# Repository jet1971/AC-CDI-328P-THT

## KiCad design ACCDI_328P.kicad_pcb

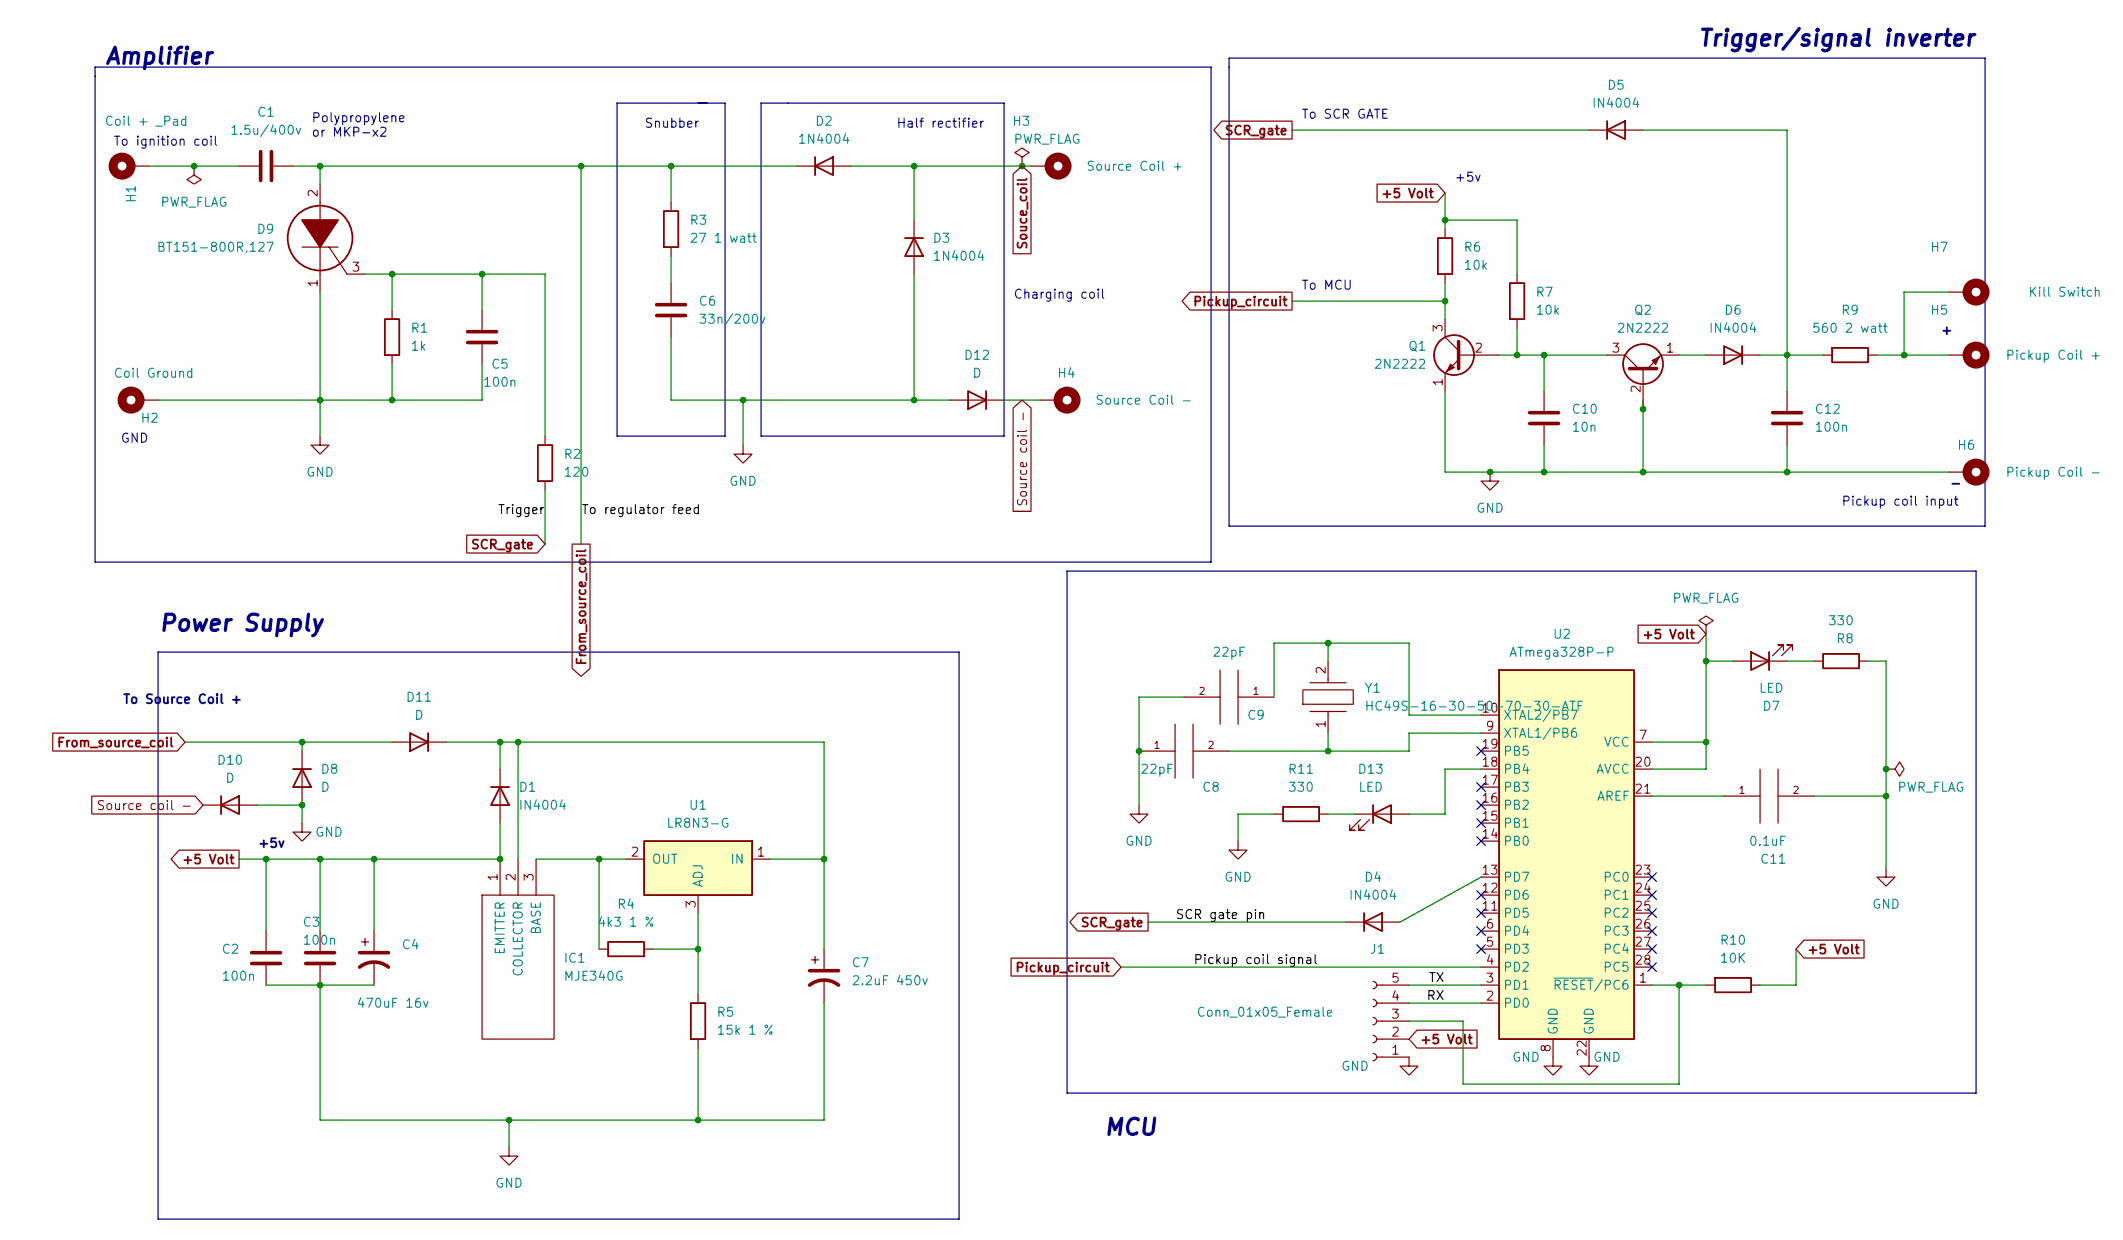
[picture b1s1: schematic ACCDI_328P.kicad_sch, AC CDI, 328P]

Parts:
C1: 1.5u/400v; C_Rect_L26.5mm_W5.0mm_P22.50mm_MKS4
C2, C3, C5, C12: 100n; C_Disc_D6.0mm_W2.5mm_P5.00mm
C4: 470uF 16v; C_Radial_D10.0mm_H16.0mm_P5.00mm
C6: 33n/200v; C_Rect_L9.0mm_W3.2mm_P7.50mm_MKT
C7: 2.2uF 450v; C_Radial_D10.0mm_H12.5mm_P5.00mm
C8, C9: 22pF; C_Disc_D5.0mm_W2.5mm_P5.00mm
C10: 10n; C_Disc_D6.0mm_W2.5mm_P5.00mm
C11: 0.1uF; C_Disc_D6.0mm_W2.5mm_P5.00mm
D1, D4, D5, D6: IN4004; D_DO-41_SOD81_P10.16mm_Horizontal
D2, D3: 1N4004; D_DO-41_SOD81_P10.16mm_Horizontal
D7, D13: LED; LED_D3.0mm
D8, D10, D11, D12: D; D_DO-41_SOD81_P10.16mm_Horizontal
D9: BT151-800R,127; TO254P470X1000X2000-3P; Manufacturer_Part_Number BT151-800R,127; Mouser Part Number 771-BT151-800R127
H1: Coil + _Pad; MountingHole_2.2mm_M2_ISO14580_Pad_TopBottom
H2: Coil Ground; MountingHole_2.2mm_M2_Pad_TopBottom
H3: Source Coil +; MountingHole_2.2mm_M2_Pad_TopBottom
H4: Source Coil -; MountingHole_2.2mm_M2_Pad_TopBottom
H5: Pickup Coil +; MountingHole_2.2mm_M2_Pad_TopBottom
H6: Pickup Coil -; MountingHole_2.2mm_M2_Pad_TopBottom
H7: Kill Switch; MountingHole_2.2mm_M2_Pad_TopBottom
IC1: MJE340G; TO229P300X760X1364-3P; Manufacturer_Part_Number MJE340G; Mouser Part Number 863-MJE340G
J1: Conn_01x05_Female; PinSocket_1x05_P2.54mm_Vertical
Q1, Q2: 2N2222; TO-92_Inline
R1: 1k; R_Axial_DIN0309_L9.0mm_D3.2mm_P12.70mm_Horizontal
R2: 120; R_Axial_DIN0309_L9.0mm_D3.2mm_P12.70mm_Horizontal
R3: 27 1 watt; R_Axial_DIN0516_L15.5mm_D5.0mm_P20.32mm_Horizontal
R4: 4k3 1 %; R_Axial_DIN0309_L9.0mm_D3.2mm_P12.70mm_Horizontal
R5: 15k 1 %; R_Axial_DIN0309_L9.0mm_D3.2mm_P12.70mm_Horizontal
R6, R7: 10k; R_Axial_DIN0309_L9.0mm_D3.2mm_P12.70mm_Horizontal
R8, R11: 330; R_Axial_DIN0309_L9.0mm_D3.2mm_P12.70mm_Horizontal
R9: 560 2 watt; R_Axial_DIN0516_L15.5mm_D5.0mm_P20.32mm_Horizontal
R10: 10K; R_Axial_DIN0207_L6.3mm_D2.5mm_P10.16mm_Horizontal
U1: LR8N3-G; TO-92_Inline
U2: ATmega328P-P; DIP-28_W7.62mm
Y1: HC49S-16-30-50-70-30-ATF; Resonator-2Pin_W10.0mm_H5.0mm; Manufacturer_Part_Number HC49S-16-30-50-70-30-ATF

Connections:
+5 Volt: C2.1, C3.1, C4.1, D1.2 (A), D7.2 (A), IC1.1 (EMITTER), J1.2, R6.1, R7.1, R10.1, U2.7 (VCC), U2.20 (AVCC)
/RX: J1.4, U2.2 (PD0)
/TX: J1.5, U2.3 (PD1)
From_source_coil: C1.1, D2.1 (K), D8.1 (K), D9.2, D11.2 (A), R3.1
GND: C2.2, C3.2, C4.2, C5.2, C6.2, C7.2, C8.1, C9.2, C10.2, C11.2, C12.2, D3.2 (A), D8.2 (A), D9.1, D10.2 (A), D12.2 (A), H2.1, H6.1, J1.1, Q1.1 (E), Q2.2 (B), R1.2, R5.2, R8.2, R11.1, U2.8 (GND), U2.22 (GND)
unnamed: C1.2, H1.1
unnamed: C5.1, D9.3, R1.1, R2.1
unnamed: C6.1, R3.2
unnamed: C7.1, D1.1 (K), D11.1 (K), IC1.2 (COLLECTOR), U1.1 (IN)
unnamed: C8.2, U2.9 (XTAL1/PB6), Y1.1
unnamed: C9.1, U2.10 (XTAL2/PB7), Y1.2
unnamed: C10.1, Q1.2 (B), Q2.3 (C), R7.2
unnamed: C11.1, U2.21 (AREF)
unnamed: C12.1, D5.2 (A), D6.1 (K), R9.2
unnamed: D4.2 (A), U2.13 (PD7)
unnamed: D6.2 (A), Q2.1 (E)
unnamed: D7.1 (K), R8.1
unnamed: D13.1 (K), R11.2
unnamed: H5.1, H7.1, R9.1
unnamed: IC1.3 (BASE), R4.1, U1.2 (OUT)
unnamed: J1.3, R10.2, U2.1 (~RESET/PC6)
unnamed: R4.2, R5.1, U1.3 (ADJ)
unnamed: D13.2 (A), U2.18 (PB4)
Pickup_circuit: Q1.3 (C), R6.2, U2.4 (PD2)
SCR_gate: D4.1 (K), D5.1 (K), R2.2
Souce_coil: D2.2 (A), D3.1 (K), H3.1
Source coil -: D10.1 (K), D12.1 (K), H4.1

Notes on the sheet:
Power Supply
MCU
Snubber
To ignition coil
Trigger/signal inverter
Charging coil
To SCR GATE
Polypropylene or MKP-x2
Half rectifier
+5v
Pickup coil input
Amplifier
To Source Coil +
GND
+5v
To MCU

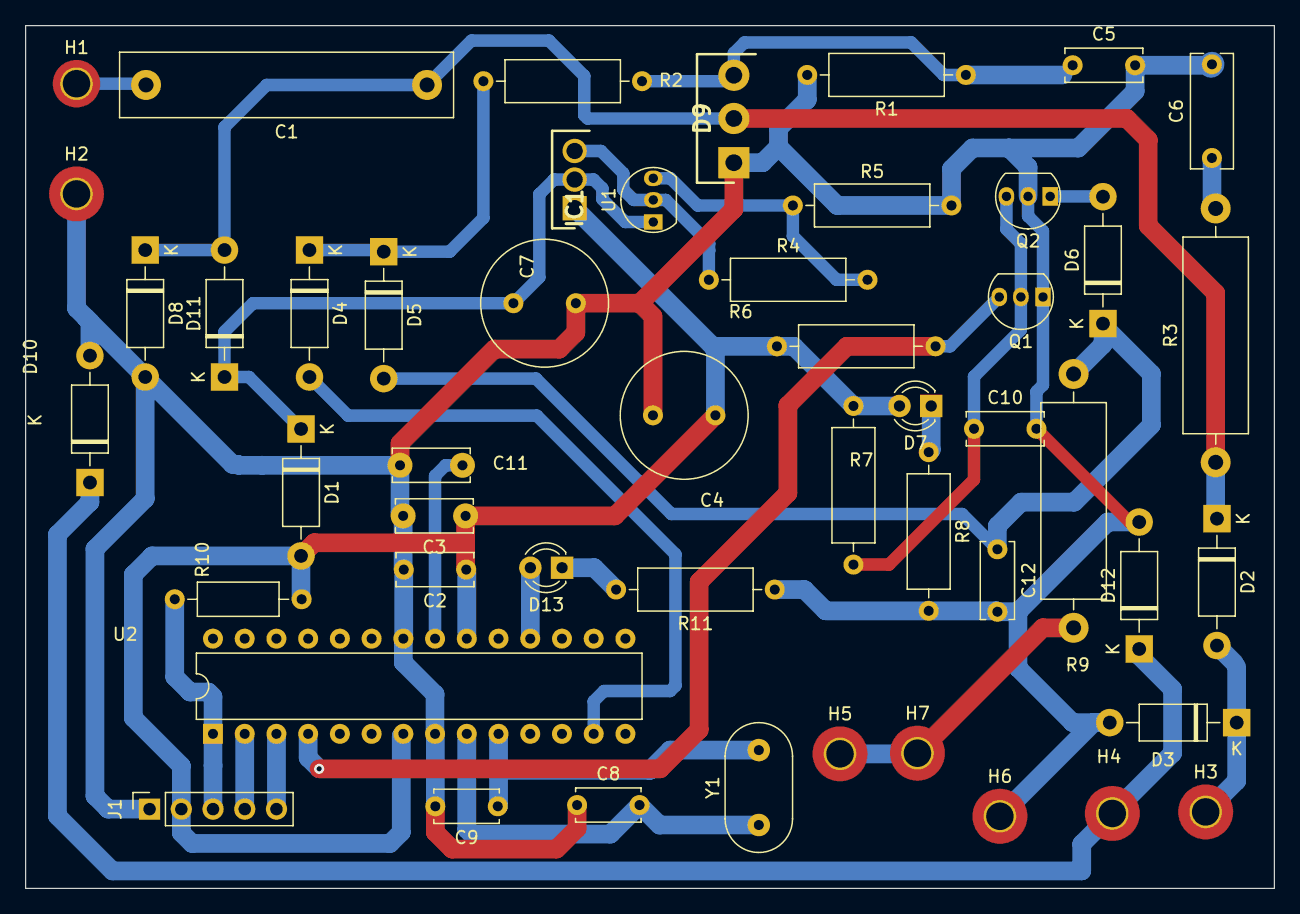
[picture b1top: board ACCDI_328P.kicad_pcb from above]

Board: 2 copper layers, 100.0 x 69.1 mm, 50 parts (0 on the bottom side), 27 nets.

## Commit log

2022-08-24 First commt
2022-08-24 version 0.2
2022-08-24 2 layer board
2022-08-25 Modified track widths
2022-08-29 Removed zenner diode
2022-08-31 Diodes and reroute
